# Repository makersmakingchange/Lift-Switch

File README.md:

<!---  Open Source Assistive Technology: GitHub Readme Template Version 1.1 (2024-Mar-15)  --->

<!-- TITLE --->
# Lift Switch
<!--- SUMMARY -->
<!-- A brief summary of the project. What it does, who it is for, how much it costs. -->
The Lift Switch is a device that modifies the output from your assistive switch. The primary case is for a user who would prefer to rest on their switch and lift off of it to activate it, instead of requiring the user to hover over the switch. There are four operating modes: momentary, latching, timed latch, and reverse acting, described below:
- Momentary: The output will turn on momentarily when you lift off of the assistive switch.
- Latching: The output toggles between on/off when you lift off of the assistive switch.
- Timed Latch: The output will turn on for a set amount of time (7s) when you lift off of the assistive switch.
- Reverse Acting: Reverses the action of an assistive switch. Assistive switch off (not activated) = Lift Switch on, Assistive switch on (activated) = Lift Switch off.

The Lift Switch can also be used as a mouse click in any of the above modes, by plugging the Lift Switch into a computer through a USB cable.

The total cost of materials to build this device is around \$75 (plus component shipping). The cost of materials per unit is around \$43 (plus component shipping) if you are able to build in bulk.

## Makers Making Change Assistive Device Library Listing
- https://www.makersmakingchange.com/s/product/lift-switch/01tJR000003UiczYAC

## How to Obtain the Device
### 1. Do-it-Yourself (DIY) or Do-it-Together (DIT)

This is an open-source assistive technology, so anyone is free to build it. All of the files and instructions required to build the device are contained within this repository. Refer to the Maker Guide below.

### 2. Request a build of this device

You may also submit a build request through the [Makers Making Change Assistive Device Library Listing](https://www.makersmakingchange.com/s/product/lift-switch/01tJR000003UiczYAC) to have a volunteer maker build the device. As the requestor, you are responsible for reimbursing the maker for the cost of materials and any shipping.

### 3. Build this device for someone else

If you have the skills and equipment to build this device, and would like to donate your time to create the device for someone who needs it, visit the [MMC Maker Wanted](https://makersmakingchange.com/maker-wanted/) section.

## Build Instructions

### 1. Read through the Maker Guide

The [Maker Guide](/Documentation/Lift_Switch_Maker_Guide.pdf) contains all the necessary information to build this device, including tool lists, assembly instructions, programming instructions and testing.

### 2. Order the Off-The-Shelf Components

The [Bill of Materials](/Documentation/Lift_Switch_BOM.csv) lists all of the parts and components required to build the device.

### 3. Order the Custom PCB

This device requires a custom PCB. Instructions are provided in the [Maker Guide](/Documentation/Lift_Switch_Maker_Guide.pdf) and the PCB fabrication files are available in the [PCB Build Files](/Build_Files/PCB_Build_Files).

### 4. Print the 3D Printable components

All of the files and individual print files can be in the [/Build_Files/3D_Printing_Files](/Build_Files/3D_Printing_Files/) folder.

### 5. Assemble the Lift Switch

Reference the [Maker Guide](/Documentation/Lift_Switch_Maker_Guide.pdf) for the tools and steps required to build each portion.

## How to improve this Device
As open source assistive technology, you are welcomed and encouraged to improve upon the design. 

## Files
### Documentation
| Document             | Version | Link |
|----------------------|---------|------|
| Maker Guide          | 1.0     | [Lift_Switch_Maker_Guide](/Documentation/Lift_Switch_Maker_Guide.pdf)     |
| Bill of Materials    | 1.0     | [Lift_Switch_Bill_of_Materials](/Documentation/Lift_Switch_BOM.csv)     |
| User Guide           | 1.0     | [Lift_Switch_User_Guide](/Documentation/Lift_Switch_User_Guide.pdf)    |
| Changelog            | 1.0     | [Changelog](CHANGES.txt)     |

### Design Files
<!---
DESIGN FILES
Include a copy of the original design files to facilitate easy editing and customization. Consider also including a generic format (e.g., STEP)
--->
 - [CAD Files](/Design_Files/CAD_Design_Files)
 - [PCB Files](/Design_Files/PCB_Design_Files)

<!---
BUILD FILES
Include a copy of the build files intended for manufacturing. This may include svg files for laser cutting, stl files for 3d printing, Gerber files for custom PCBs, and Arduino files for custom firmware
--->
### Build Files
 - [3D Printing Files](/Build_Files/3D_Printing_Files)
 - [PCB Build Files](/Build_Files/PCB_Build_Files)
 - [Firmware Files](/Build_Files/Firmware_Files)

<!---
ATTRIBUTION
Provide any necessary attribution for designs or components that are included in the device or as part of the project.
--->
## Attribution

The Lift Switch was designed by the Rehabilitation Engineering Department at Horizon Health's Stan Cassidy Centre for Rehabilitation (SCCR). Development was supported through the Government of Canada's Innovation Science and Economic Development  [Accessible Technology Program](https://ised-isde.canada.ca/site/accessible-technology-program). The ATP program enabled SCCR to deploy numerous Lift Switches to users at reduced cost.

The latest design (V2.0) incorporates feedback and suggestions from numerous users, clinicians, and volunteer makers.

The latest design incorporates several commercially available open source hardware components from [Adafruit](https://www.adafruit.com/). The Lift Switch firmware utilizes the [Arduino](https://www.arduino.cc/) development platform, and a number of libraries developed and shared by the open source community.

<!---
This is the attribution for the template.
--->
The documentation template was created by Makers Making Change / Neil Squire Society and is used under a CC BY-SA 4.0 license. It is available at the following link: [https://github.com/makersmakingchange/OpenAT-Template](https://github.com/makersmakingchange/OpenAT-Template)

<!---
CONTRIBUTORS
List the names of the people that contributed to the design. This could include the original source of the idea, designers, testers, documenters, etc.
--->
### Contributors

- Rachelle Bernier, Horizon Health Network.
- Marla Calder, Horizon Health Network
- Natasha Hanson, Horizon Health Network
- Dorian Hawkes, Horizon Health Network
- Rick McCaskill, Horizon Health Network
- Billie O'Connor, Horizon Health Network
- Kristen Culberson, Horizon Health Network
- Josie Versloot, Neil Squire Society / Makers Making Change

<!---
LICENSE
Add the year(s) for the copyright and the Designer Name. You may use the standard set of open licenses or choose your own for the hardware, software, and accompanying materials.
--->
## License
Copyright (c) 2020-2024 Stan Cassidy Centre for Rehabilitation.

This repository describes Open Hardware:
 - Everything needed or used to design, make, test, or prepare the Lift Switch is licensed under the [CERN 2.0 Weakly Reciprocal license (CERN-OHL-W v2) or later](https://cern.ch/cern-ohl ) .
 - All software is under the [GNU General Public License v3.0 (GPL-3.0)](https://www.gnu.org/licenses/gpl.html).
 - Accompanying material such as instruction manuals, videos, and other copyrightable works that are useful but not necessary to design, make, test, or prepare the Lift Switch are published under a [Creative Commons Attribution-ShareAlike 4.0 license (CC BY-SA 4.0)](https://creativecommons.org/licenses/by-sa/4.0/) .

You may redistribute and modify this documentation and make products using it under the terms of the [CERN-OHL-W v2](https://cern.ch/cern-ohl).
This documentation is distributed WITHOUT ANY EXPRESS OR IMPLIED WARRANTY, INCLUDING OF MERCHANTABILITY, SATISFACTORY QUALITY AND FITNESS FOR A PARTICULAR PURPOSE.
Please see the CERN-OHL-W v2 for applicable conditions.

Source Location: https://github.com/makersmakingchange/Lift-Switch

----

<!-- ABOUT MMC START -->
## About Makers Making Change

Makers Making Change is a program of [Neil Squire](https://www.neilsquire.ca/), a Canadian non-profit that uses technology, knowledge, and passion to empower people with disabilities.

Makers Making Change leverages the capacity of community based Makers, Disability Professionals and Volunteers to develop and deliver affordable Open Source Assistive Technologies.

 - Website: [www.MakersMakingChange.com](https://www.makersmakingchange.com/)
 - GitHub: [makersmakingchange](https://github.com/makersmakingchange)
 - Bluesky: [@makersmakingchange.bsky.social](https://bsky.app/profile/makersmakingchange.bsky.social)
 - Instagram: [@makersmakingchange](https://www.instagram.com/makersmakingchange)
 - Facebook: [makersmakechange](https://www.facebook.com/makersmakechange)
 - LinkedIn: [Neil Squire Society](https://www.linkedin.com/company/neil-squire-society/)
 - Thingiverse: [makersmakingchange](https://www.thingiverse.com/makersmakingchange/about)
 - Printables: [MakersMakingChange](https://www.printables.com/@MakersMakingChange)

### Contact Us
For technical questions, to get involved, or to share your experience we encourage you to [visit our website](https://www.makersmakingchange.com/) or [contact us](https://www.makersmakingchange.com/s/contact).
<!-- ABOUT MMC END -->

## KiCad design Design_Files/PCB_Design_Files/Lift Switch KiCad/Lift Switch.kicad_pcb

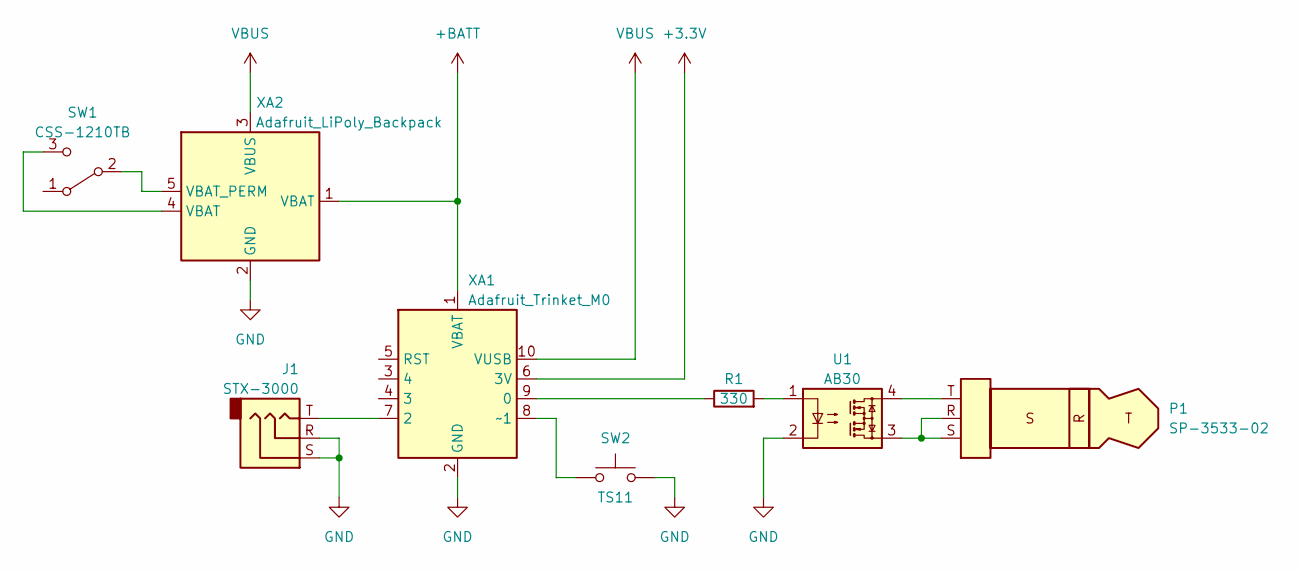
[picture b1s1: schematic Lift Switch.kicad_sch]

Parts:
J1: STX-3000
P1: SP-3533-02
R1: 330; R_Axial_DIN0207_L6.3mm_D2.5mm_P7.62mm_Horizontal
SW1: CSS-1210TB
SW2: TS11; TS11-674-XX-BK-XXX-RA-D
U1: AB30; DIP-4_W7.62mm
XA1: Adafruit_Trinket_M0; Adafruit Trinket M0
XA2: Adafruit_LiPoly_Backpack; Adafruit LiPoly Backpack

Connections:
+3.3V: XA1.6 (3V)
+BATT: XA1.1 (VBAT), XA2.1 (VBAT)
GND: J1.R, J1.S, SW2.2, U1.2, XA1.2 (GND), XA1.11 (MNT), XA1.12 (MNT), XA2.2 (GND), XA2.6 (MNT)
unnamed: J1.T, XA1.7 (2)
unnamed: P1.R, P1.S, U1.3
unnamed: P1.T, U1.4
unnamed: R1.1, XA1.9 (0)
unnamed: R1.2, U1.1
unnamed: SW1.2 (B), XA2.5 (VBAT_PERM)
unnamed: SW1.3 (C), XA2.4 (VBAT)
unnamed: SW2.1, XA1.8 (~1)
VBUS: XA1.10 (VUSB), XA2.3 (VBUS)

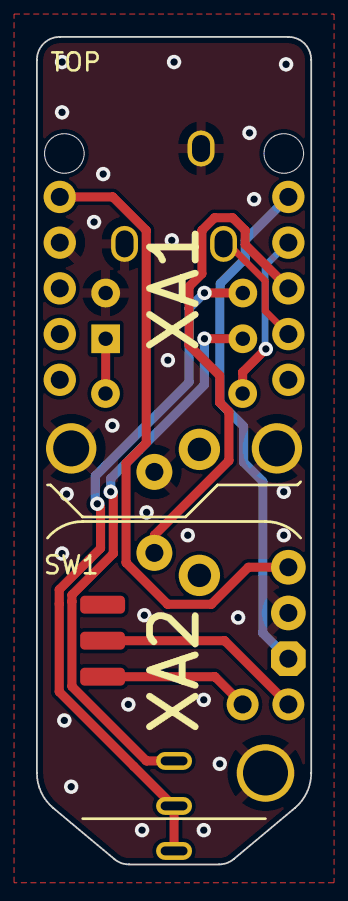
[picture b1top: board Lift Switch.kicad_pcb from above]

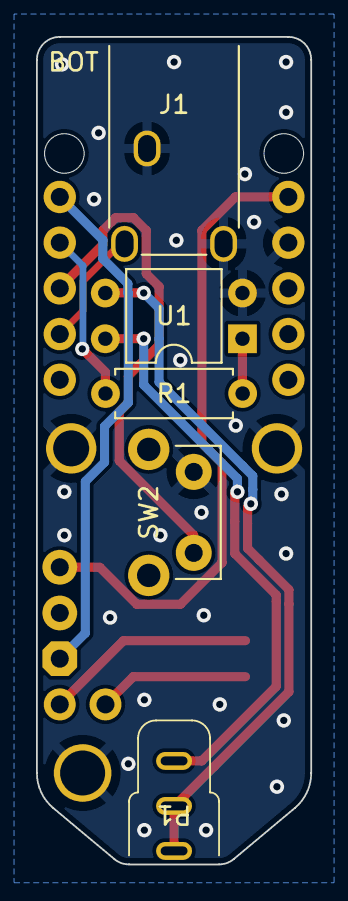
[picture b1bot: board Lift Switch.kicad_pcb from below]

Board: 2 copper layers, 15.2 x 46.0 mm, 8 parts (5 on the bottom side), 11 nets.

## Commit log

2024-03-28 Initial commit files
2024-03-28 Initial documentation commit
2025-04-10 Add Update About MMC GitHub Action
2025-04-12 Update About MMC Section
2026-02-23 Updated enclosure files

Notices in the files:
README.md:
List of open source licenses. Hardware: CERN-OHL-W-2.0, Software: GPL-3.0-or-later, Documentation: CC-BY-SA-4.0.
